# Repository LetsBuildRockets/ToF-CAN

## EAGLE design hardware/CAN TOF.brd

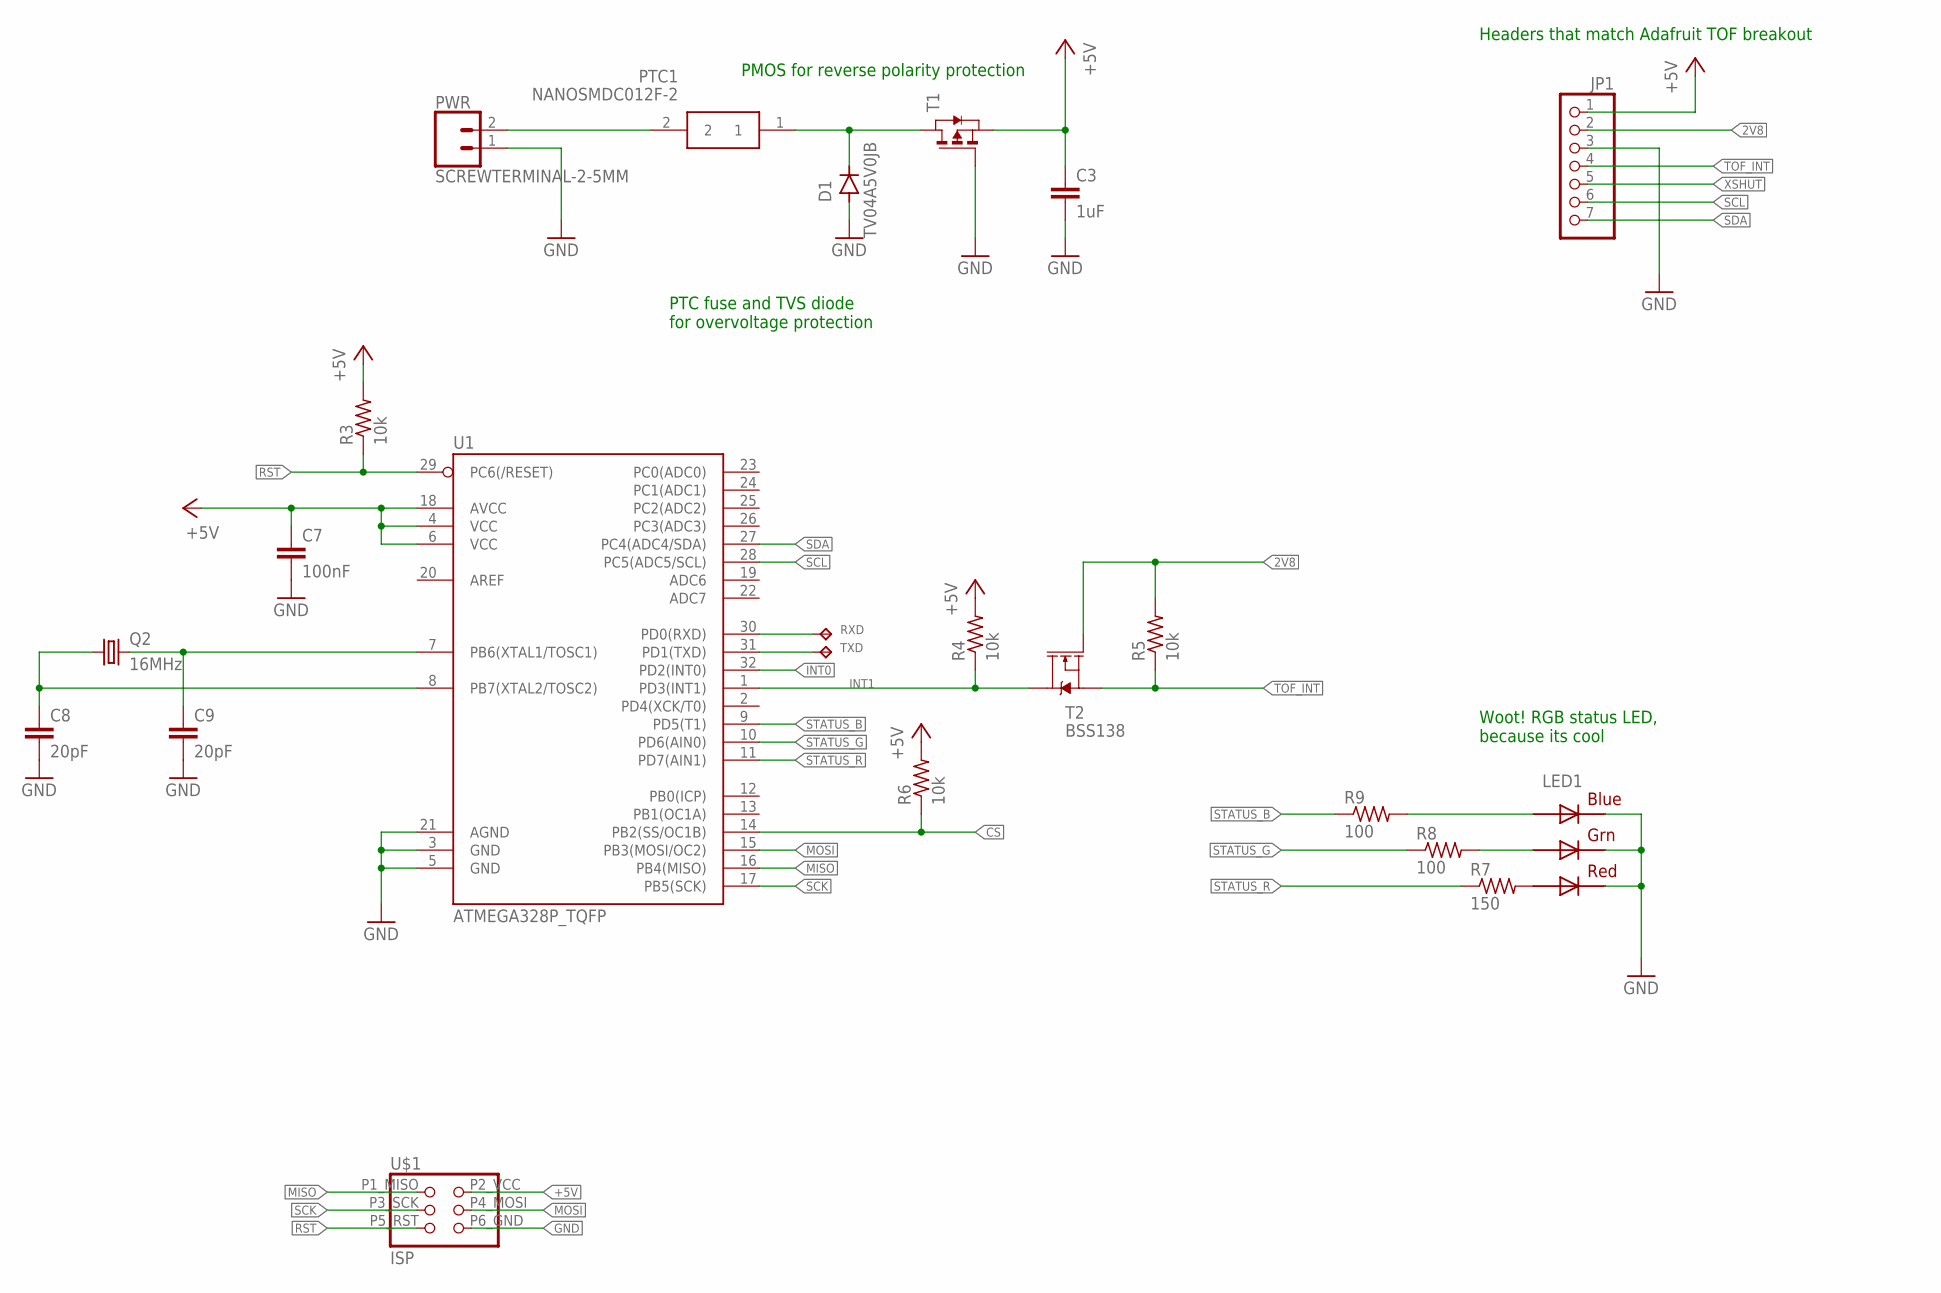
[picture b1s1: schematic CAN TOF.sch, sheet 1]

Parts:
C3: 1uF; C0805
C7: 100nF; C0402
C8, C9: 20pF; C0402
D1: TV04A5V0JB; SMA-DO214AC
JP1: PINHD-1X7; 1X07
LED1: RGBLED5050
PTC1: NANOSMDC012F-2; FUSC3216X100N
PWR: SCREWTERMINAL-2-5MM; SCREWTERMINAL-5MM-2
Q2: 16MHz; CTS406
R3, R4, R5, R6: 10k; R0805
R7: 150; R0805
R8, R9: 100; R0805
RXD: TPB1,27; B1,27
T1: PMOSSOT23; SOT-23
T2: BSS138; SOT23-3
TXD: TPB1,27; B1,27
U1: ATMEGA328P_TQFP; TQFP32-08
U$1: ISP

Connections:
2V8: JP1.2, R5.2, T2.1 (G)
+5V: C3.1, C7.1, JP1.1, R3.2, R4.2, R6.2, T1.2 (S), U1.4 (VCC), U1.6 (VCC), U1.18 (AVCC), U$1.P2_VCC (VCC); also elsewhere on the board
CS: R6.1, U1.14 (PB2(SS/OC1B)); also elsewhere on the board
GND: C3.2, C7.2, C8.2, C9.2, D1.A, JP1.3, LED1.4 (BLUE_C), LED1.5 (RED_C), LED1.6 (GREEN_C), PWR.1, T1.3 (G), U1.3 (GND), U1.5 (GND), U1.21 (AGND), U$1.P6_GND (GND); also elsewhere on the board
INT0: U1.32 (PD2(INT0)); also elsewhere on the board
INT1: R4.1, T2.3 (D), U1.1 (PD3(INT1))
MISO: U1.16 (PB4(MISO)), U$1.P1_MISO (MISO); also elsewhere on the board
MOSI: U1.15 (PB3(MOSI/OC2)), U$1.P4_MOSI (MOSI); also elsewhere on the board
unnamed: RXD.TP, U1.30 (PD0(RXD))
unnamed: TXD.TP, U1.31 (PD1(TXD))
unnamed: PTC1.2, PWR.2
unnamed: D1.K (C), PTC1.1, T1.1 (D)
unnamed: LED1.2 (RED_A), R7.2
unnamed: LED1.1 (GREEN_A), R8.2
unnamed: LED1.3 (BLUE_A), R9.2
unnamed: C8.1, Q2.1, U1.8 (PB7(XTAL2/TOSC2))
unnamed: C9.1, Q2.3 (2), U1.7 (PB6(XTAL1/TOSC1))
RST: R3.1, U1.29 (PC6(/RESET)), U$1.P5_RST (RST)
SCK: U1.17 (PB5(SCK)), U$1.P3_SCK (SCK); also elsewhere on the board
SCL: JP1.6, U1.28 (PC5(ADC5/SCL))
SDA: JP1.7, U1.27 (PC4(ADC4/SDA))
STATUS_B: R9.1, U1.9 (PD5(T1))
STATUS_G: R8.1, U1.10 (PD6(AIN0))
STATUS_R: R7.1, U1.11 (PD7(AIN1))
TOF_INT: JP1.4, R5.1, T2.2 (S)
XSHUT: JP1.5

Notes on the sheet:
PTC fuse and TVS diode for overvoltage protection
PMOS for reverse polarity protection
Headers that match Adafruit TOF breakout
Woot! RGB status LED, because its cool

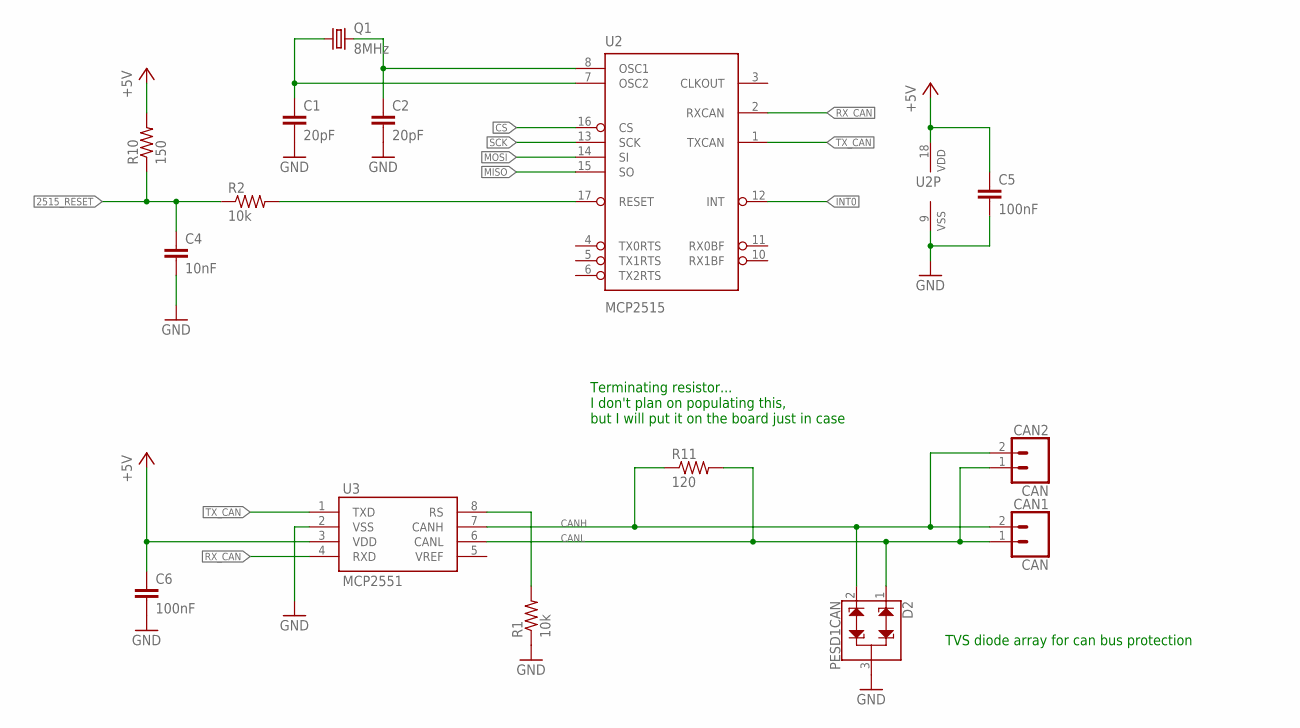
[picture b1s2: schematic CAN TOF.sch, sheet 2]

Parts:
C1, C2: 20pF; C0402
C4: 10nF; C0402
C5, C6: 100nF; C0402
CAN1, CAN2: CAN; SCREWTERMINAL-5MM-2
D2: PESD1CAN; SOT23-3
Q1: 8MHz; CTS406
R1, R2: 10k; R0805
R10: 150; R0805
R11: 120; R0805
U2: MCP2515; SO18W
U3: MCP2551; SO08

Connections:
2515_RESET: C4.1, R2.1, R10.1
+5V: C5.1, C6.1, R10.2, U2.18 (VDD), U3.3 (VDD); also elsewhere on the board
CANH: CAN1.2, CAN2.2, D2.2, R11.1, U3.7 (CANH)
CANL: CAN1.1, CAN2.1, D2.1, R11.2, U3.6 (CANL)
CS: U2.16 (CS); also elsewhere on the board
GND: C1.2, C2.2, C4.2, C5.2, C6.2, D2.3, R1.1, U2.9 (VSS), U3.2 (VSS); also elsewhere on the board
INT0: U2.12 (INT); also elsewhere on the board
MISO: U2.15 (SO); also elsewhere on the board
MOSI: U2.14 (SI); also elsewhere on the board
unnamed: R1.2, U3.8 (RS)
unnamed: R2.2, U2.17 (RESET)
unnamed: C1.1, Q1.1, U2.7 (OSC2)
unnamed: C2.1, Q1.3 (2), U2.8 (OSC1)
RX_CAN: U2.2 (RXCAN), U3.4 (RXD)
SCK: U2.13 (SCK); also elsewhere on the board
TX_CAN: U2.1 (TXCAN), U3.1 (TXD)

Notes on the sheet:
TVS diode array for can bus protection
Terminating resistor... I don't plan on populating this, but I will put it on the board just in case

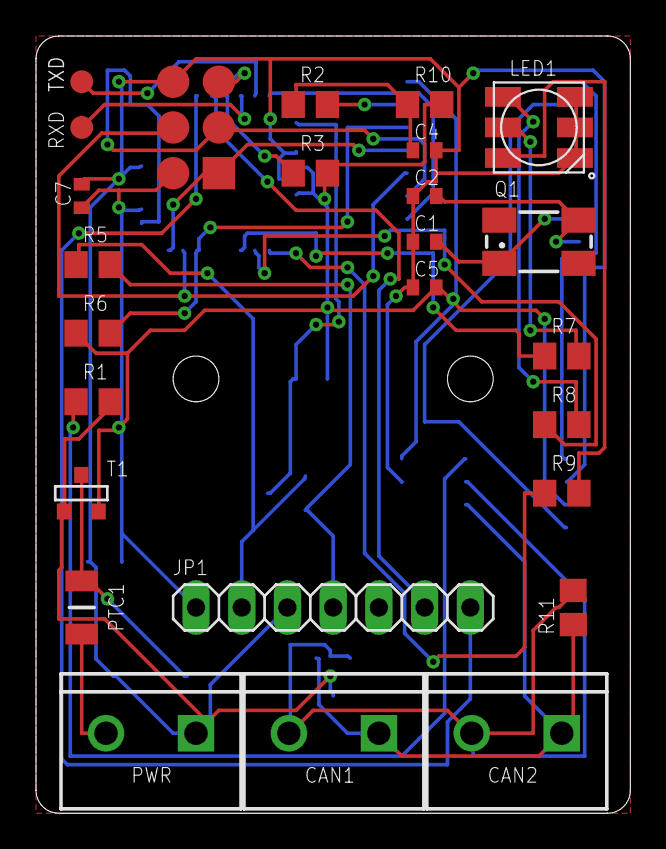
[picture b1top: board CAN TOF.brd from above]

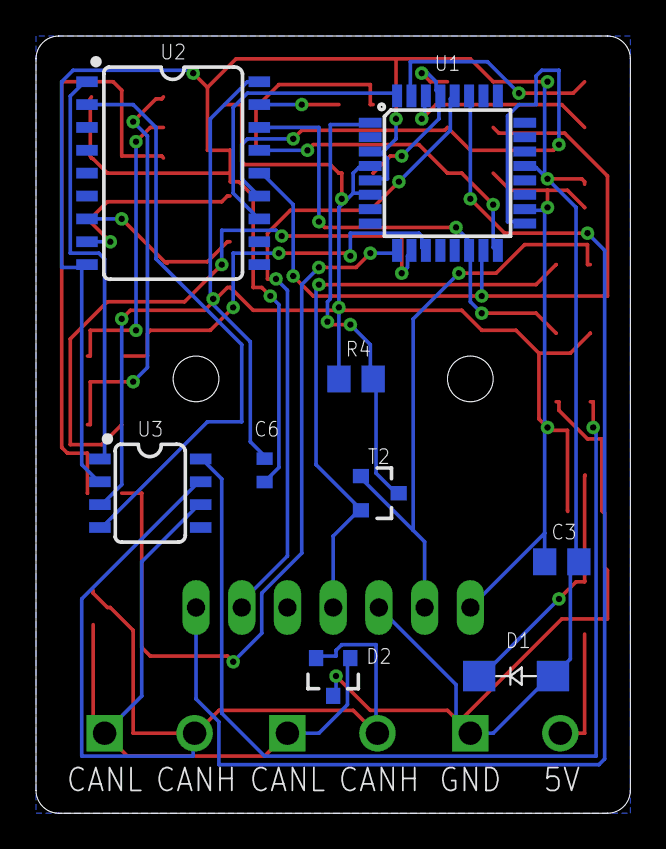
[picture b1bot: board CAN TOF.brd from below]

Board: 2 copper layers, 33.0 x 43.2 mm, 35 parts (9 on the bottom side), 32 nets.

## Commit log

2019-02-14 init with hardware files
2019-02-19 started some firmware...
2019-03-01 switching to atmel studio. also there are proj files here. sue me.
2019-03-01 ok hopefully we have i2c and VL53L0X support(?)
2019-03-01 ok so this reads out the distance from the ToF sensor and prints over UART
2019-03-01 oops wrong pin numbers
2019-03-02 ok we can init comms with the MCP2515, but can it send CAN data?
2019-03-02 ok. time to test with roborio
2019-03-02 stared java code based on team1904's work
2019-03-02 switching to 20Mhz crystal...
2019-03-03 thickened up the case, and fixed component clearance issues
2019-03-20 wow, firmware is working, error codes, status light and all
2019-03-20 removed commented out code
2019-03-20 add a little clearance to the screw terminals
2019-03-20 added a little more clearance to the case and added some labels
2019-03-20 classes all done, i guess, also added example code
2019-03-22 updated the case a smidge, added some mech. drawings, and added frc release zip
2019-03-22 added a ctrl byte
2019-03-22 idk if this filter/mask thing works yet
2019-03-23 more registers!
2019-03-26 lets recv with interrupts
2019-03-26 now i need a rio to test this...
2019-03-26 removed some extra imports
2019-03-26 some ctrl bytes! so now we can get the version number and set the address... although this needs to be tested
2019-03-26 just made the label text a little bigger
2019-04-07 v 1.1
2019-04-07 v1.1
2019-04-07 fixed error blink

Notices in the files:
parts and their libraries:
SparkFun-DiscreteSemi: Licensing: Creative Commons ShareAlike 4.0 International - https://creativecommons.org/licenses/by-sa/4.0
